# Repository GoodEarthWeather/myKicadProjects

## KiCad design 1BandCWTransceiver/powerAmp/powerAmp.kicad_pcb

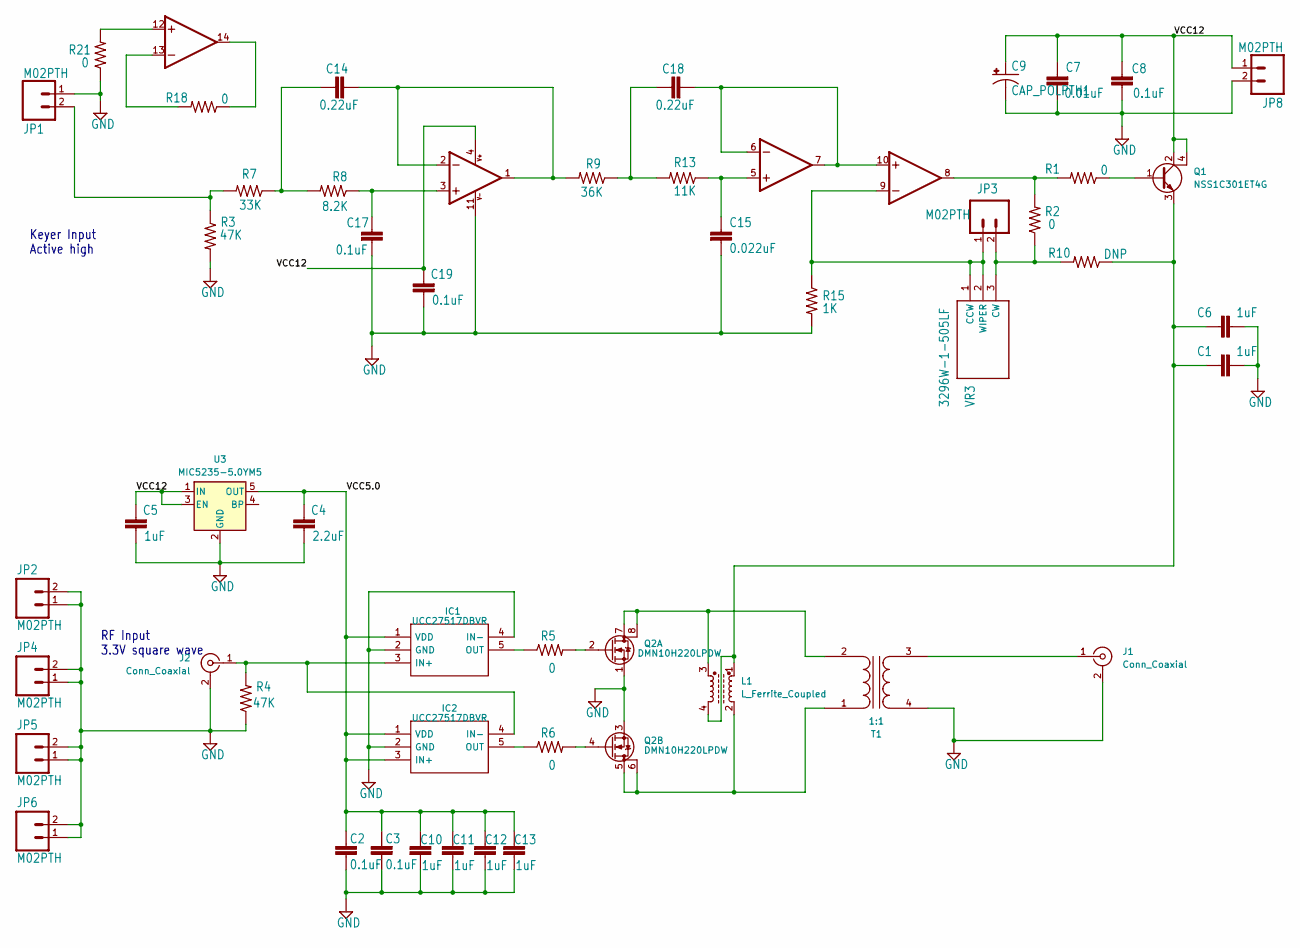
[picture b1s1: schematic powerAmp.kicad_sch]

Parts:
C1, C5, C6, C10, C11, C12, C13: 1uF; C_0603_1608Metric_Pad1.08x0.95mm_HandSolder
C2, C3, C8, C19: 0.1uF; C_0603_1608Metric_Pad1.08x0.95mm_HandSolder
C4: 2.2uF; C_0603_1608Metric_Pad1.08x0.95mm_HandSolder
C7: 0.01uF; C_0603_1608Metric_Pad1.08x0.95mm_HandSolder
C9: CAP_POLPTH1; C_Radial_D5.0mm_H11.0mm_P2.00mm
C14, C18: 710-885012206073; C_0603_1608Metric_Pad1.08x0.95mm_HandSolder
C15: 80-C0603C223K3R; C_0603_1608Metric_Pad1.08x0.95mm_HandSolder
C17: 710-885012206071; C_0603_1608Metric_Pad1.08x0.95mm_HandSolder
IC1, IC2: UCC27517DBVR; SOT95P280X145-5N; Mouser Part Number 595-UCC27517DBVR
J1, J2: Conn_Coaxial; SMA_Amphenol_132289_EdgeMount
JP1, JP2, JP3, JP4, JP5, JP6, JP8: M02PTH; PinHeader_1x02_P2.54mm_Vertical
L1: L_Ferrite_Coupled; Transformer_Balun_Amidon-T50
Q1: NSS1C301ET4G; TO-252-3_TabPin4
Q2: DMN10H220LPDW; DMN10H220LPDW13
R1, R2, R18, R21: 0; R_0603_1608Metric_Pad0.98x0.95mm_HandSolder
R3, R4, R7: 603-RC0603FR-0733KL; R_0603_1608Metric_Pad0.98x0.95mm_HandSolder
R5, R6: 603-RC0603FR-0733KL; R_0805_2012Metric_Pad1.20x1.40mm_HandSolder
R8: 603-RC0603FR-078K2L; R_0603_1608Metric_Pad0.98x0.95mm_HandSolder
R9: 603-RC0603FR-0736KL; R_0603_1608Metric_Pad0.98x0.95mm_HandSolder
R10: DNP; R_0603_1608Metric_Pad0.98x0.95mm_HandSolder
R13: 603-RC0603FR-0711KL; R_0603_1608Metric_Pad0.98x0.95mm_HandSolder
R15: 603-RC0603FR-071KL; R_0603_1608Metric_Pad0.98x0.95mm_HandSolder
T1: 1:1; Transformer_Toroid_Horizontal_D14.0mm_Amidon-T50
U3: MIC5235-5.0YM5; SOT-23-5
U$2: OPA1679IDR; SOIC-14_3.9x8.7mm_P1.27mm
VR3: 3296W-1-505LF; Potentiometer_Bourns_3296W_Vertical

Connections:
/VCC5.0: C2.2, C3.2, C4.2, C10.1, C11.1, C12.1, C13.1, IC1.1 (VDD), IC2.1 (VDD), IC2.3 (IN+), U3.5 (OUT)
/VCC12: C5.2, C7.2, C8.2, C9.1 (+), C19.2, JP8.1, Q1.2 (C), Q1.4 (C), U3.1 (IN), U3.3 (EN), U$2.4 (V+)
GND: C1.1, C2.1, C3.1, C4.1, C5.1, C6.1, C7.1, C8.1, C9.2 (-), C10.2, C11.2, C12.2, C13.2, C15.2, C17.2, C19.1, IC1.2 (GND), IC1.4 (IN-), IC2.2 (GND), J1.2 (Ext), J2.2 (Ext), JP1.1, JP2.1, JP2.2, JP4.1, JP4.2, JP5.1, JP5.2, JP6.1, JP6.2, JP8.2, Q2.1 (S), Q2.3 (S), R3.2, R4.1, R15.2, R21.1, T1.4 (SB), U3.2 (GND), U$2.11 (V-)
unnamed: C14.1, R7.1, R8.2
unnamed: C18.1, R9.1, R13.2
unnamed: IC1.3 (IN+), IC2.4 (IN-), J2.1 (In), R4.2
unnamed: IC1.5 (OUT), R5.1
unnamed: IC2.5 (OUT), R6.1
unnamed: J1.1 (In), T1.3 (SA)
unnamed: JP1.2, R3.1, R7.2
unnamed: Q1.1 (B), R1.1
unnamed: C1.2, C6.2, L1.1, L1.4, Q1.3 (E), R10.1
unnamed: Q2.2 (G), R5.2
unnamed: Q2.4 (G), R6.2
unnamed: L1.2, Q2.5 (D), Q2.6 (D), T1.1 (AA)
unnamed: L1.3, Q2.7 (D), Q2.8 (D), T1.2 (AB)
unnamed: C17.1, R8.1, U$2.3 (+IN)
unnamed: C14.2, R9.2, U$2.1 (OUT), U$2.2 (-IN)
unnamed: C15.1, R13.1, U$2.5 (+IN)
unnamed: C18.2, U$2.6 (-IN), U$2.7 (OUT), U$2.10 (+IN)
unnamed: JP3.1, R15.1, U$2.9 (-IN), VR3.1 (CCW), VR3.2 (WIPER)
unnamed: R1.2, R2.2, U$2.8 (OUT)
unnamed: R21.2, U$2.12 (+IN)
unnamed: R18.2, U$2.13 (-IN)
unnamed: R18.1, U$2.14 (OUT)
unnamed: JP3.2, R2.1, R10.2, VR3.3 (CW)

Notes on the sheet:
RF Input 3.3V square wave
Keyer Input Active high

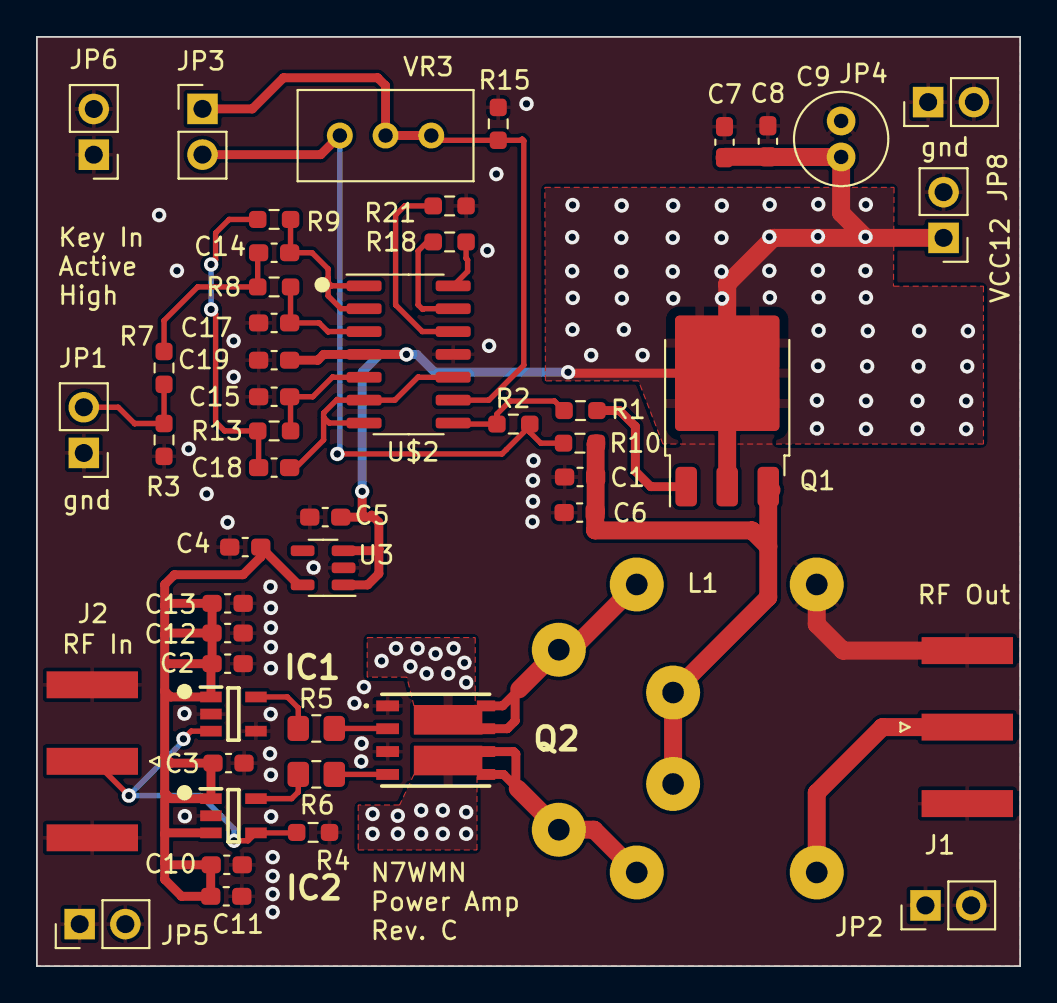
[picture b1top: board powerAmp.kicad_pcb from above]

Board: 2 copper layers, 54.6 x 51.6 mm, 50 parts (1 on the bottom side), 26 nets.

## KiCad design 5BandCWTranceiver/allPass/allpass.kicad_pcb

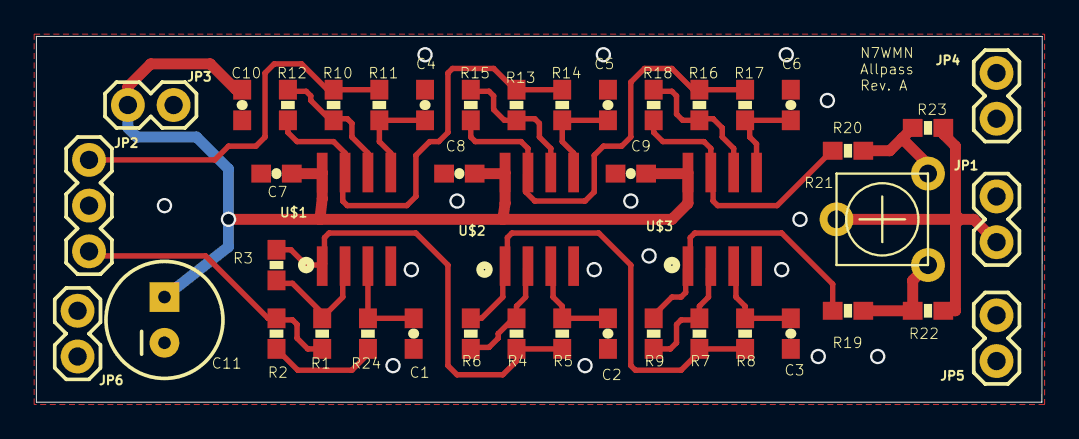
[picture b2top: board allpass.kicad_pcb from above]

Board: 2 copper layers, 55.9 x 20.3 mm, 44 parts (0 on the bottom side), 26 nets.

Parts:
C1, C2, C3, C4, C5, C6: 0.01uF; 0603-CAP
C7, C8, C9, C10: 0.1uF; 0603-CAP
C11: 100uF; CPOL-RADIAL-100UF-25V
JP1, JP3, JP4, JP5, JP6: M02PTH; 1X02
JP2: 1X03
R1, R3, R4, R6, R7, R9, R10, R12, R13, R15, R16, R18: 10K; 0603-RES
R2: 1.5K; 0603-RES
R5: 11.3K; 0603-RES
R8: 51.1K; 0603-RES
R11: 5.23K; 0603-RES
R14: 23.2K; 0603-RES
R17: 178K; 0603-RES
R19, R20: 4.7K; 0603-RES
R21: TRIMPOTPTH; TRIM_POT_PTH
R22, R23: 0; 0603-RES
R24: 200; 0603-RES
U$1, U$2, U$3: LM4562; SOIC8

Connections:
GND: C1.2, C2.2, C3.2, C4.2, C5.2, C6.2, C7.2, C8.2, C9.2, C10.2, C11.2, JP1.2, JP2.2, JP3.2, JP4.1, JP4.2, JP5.1, JP5.2, JP6.1, JP6.2, U$1.4, U$2.4, U$3.4
unnamed: R2.2, R24.1
unnamed: C1.1, R24.2, U$1.3
unnamed: R1.2, R3.1, U$1.2
unnamed: R3.2, R4.1, R5.1, U$1.1
unnamed: R4.2, R6.1, U$2.2
unnamed: C2.1, R5.2, U$2.3
unnamed: R15.2, R16.1, R17.1, U$2.7
unnamed: R6.2, R7.1, R8.1, U$2.1
unnamed: R7.2, R9.1, U$3.2
unnamed: C3.1, R8.2, U$3.3
unnamed: R16.2, R18.1, U$3.6
unnamed: R9.2, R19.1, U$3.1
unnamed: R10.2, R12.1, U$1.6
unnamed: C4.1, R11.2, U$1.5
unnamed: C6.1, R17.2, U$3.5
unnamed: R12.2, R13.1, R14.1, U$1.7
unnamed: R13.2, R15.1, U$2.6
unnamed: C5.1, R14.2, U$2.5
unnamed: R18.2, R20.1, U$3.7
unnamed: JP2.3, R1.1, R2.1
unnamed: JP2.1, R10.1, R11.1
unnamed: R20.2, R21.3, R23.1
unnamed: R19.2, R21.1, R22.2
unnamed: JP1.1, R21.2, R22.1, R23.2
VCC5: C7.1, C8.1, C9.1, C10.1, C11.1, JP3.1, U$1.8, U$2.8, U$3.8

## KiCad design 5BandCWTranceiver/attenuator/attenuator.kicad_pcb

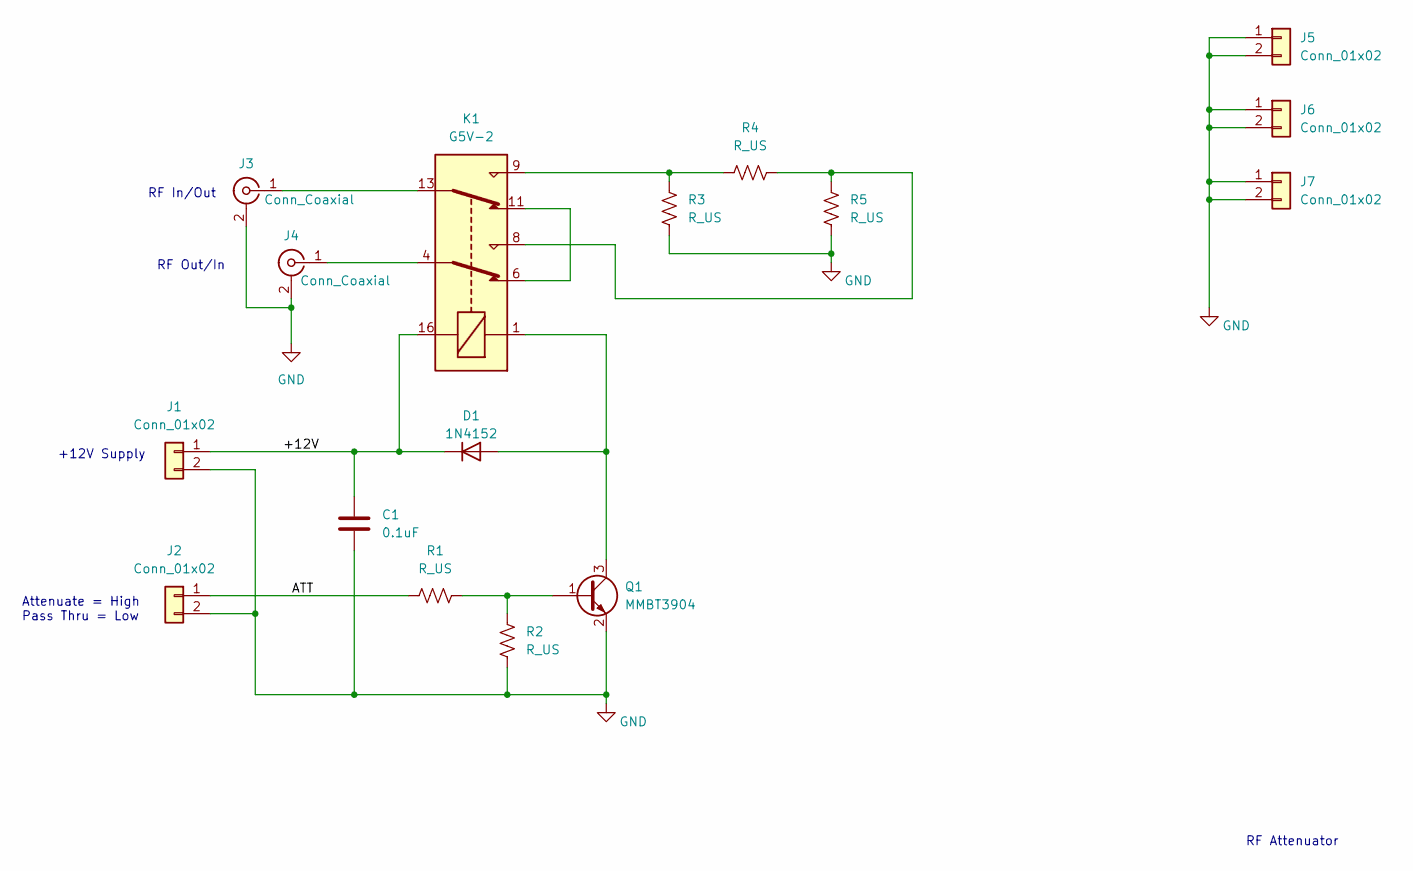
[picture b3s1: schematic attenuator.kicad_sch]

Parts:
C1: 0.1uF; C_0603_1608Metric_Pad1.08x0.95mm_HandSolder
D1: 1N4152; D_DO-41_SOD81_P7.62mm_Horizontal
J1, J2, J5, J6, J7: Conn_01x02; PinHeader_1x02_P2.54mm_Vertical
J3, J4: Conn_Coaxial; SMA_Samtec_SMA-J-P-X-ST-EM1_EdgeMount
K1: G5V-2; Relay_DPDT_Omron_G5V-2
Q1: MMBT3904; SOT-23
R1, R2, R3, R4, R5: R_US; R_0603_1608Metric_Pad0.98x0.95mm_HandSolder

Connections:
/+12V: C1.1, D1.1 (K), J1.1, K1.16
/ATT: J2.1, R1.1
GND: C1.2, J1.2, J2.2, J3.2 (Ext), J4.2 (Ext), J5.1, J5.2, J6.1, J6.2, J7.1, J7.2, Q1.2 (E), R2.2, R3.2, R5.2
unnamed: D1.2 (A), K1.1, Q1.3 (C)
unnamed: J3.1 (In), K1.13
unnamed: J4.1 (In), K1.4
unnamed: K1.8, R4.2, R5.1
unnamed: K1.9, R3.1, R4.1
unnamed: K1.6, K1.11
unnamed: Q1.1 (B), R1.2, R2.1

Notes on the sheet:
RF Out/In
RF Attenuator
Attenuate = High Pass Thru = Low
RF In/Out
+12V Supply

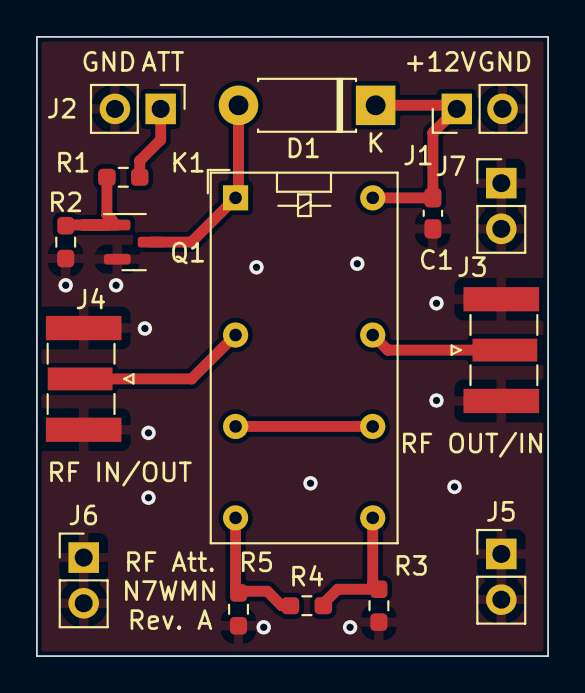
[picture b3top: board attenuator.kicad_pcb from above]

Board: 2 copper layers, 28.4 x 34.4 mm, 16 parts (0 on the bottom side), 10 nets.

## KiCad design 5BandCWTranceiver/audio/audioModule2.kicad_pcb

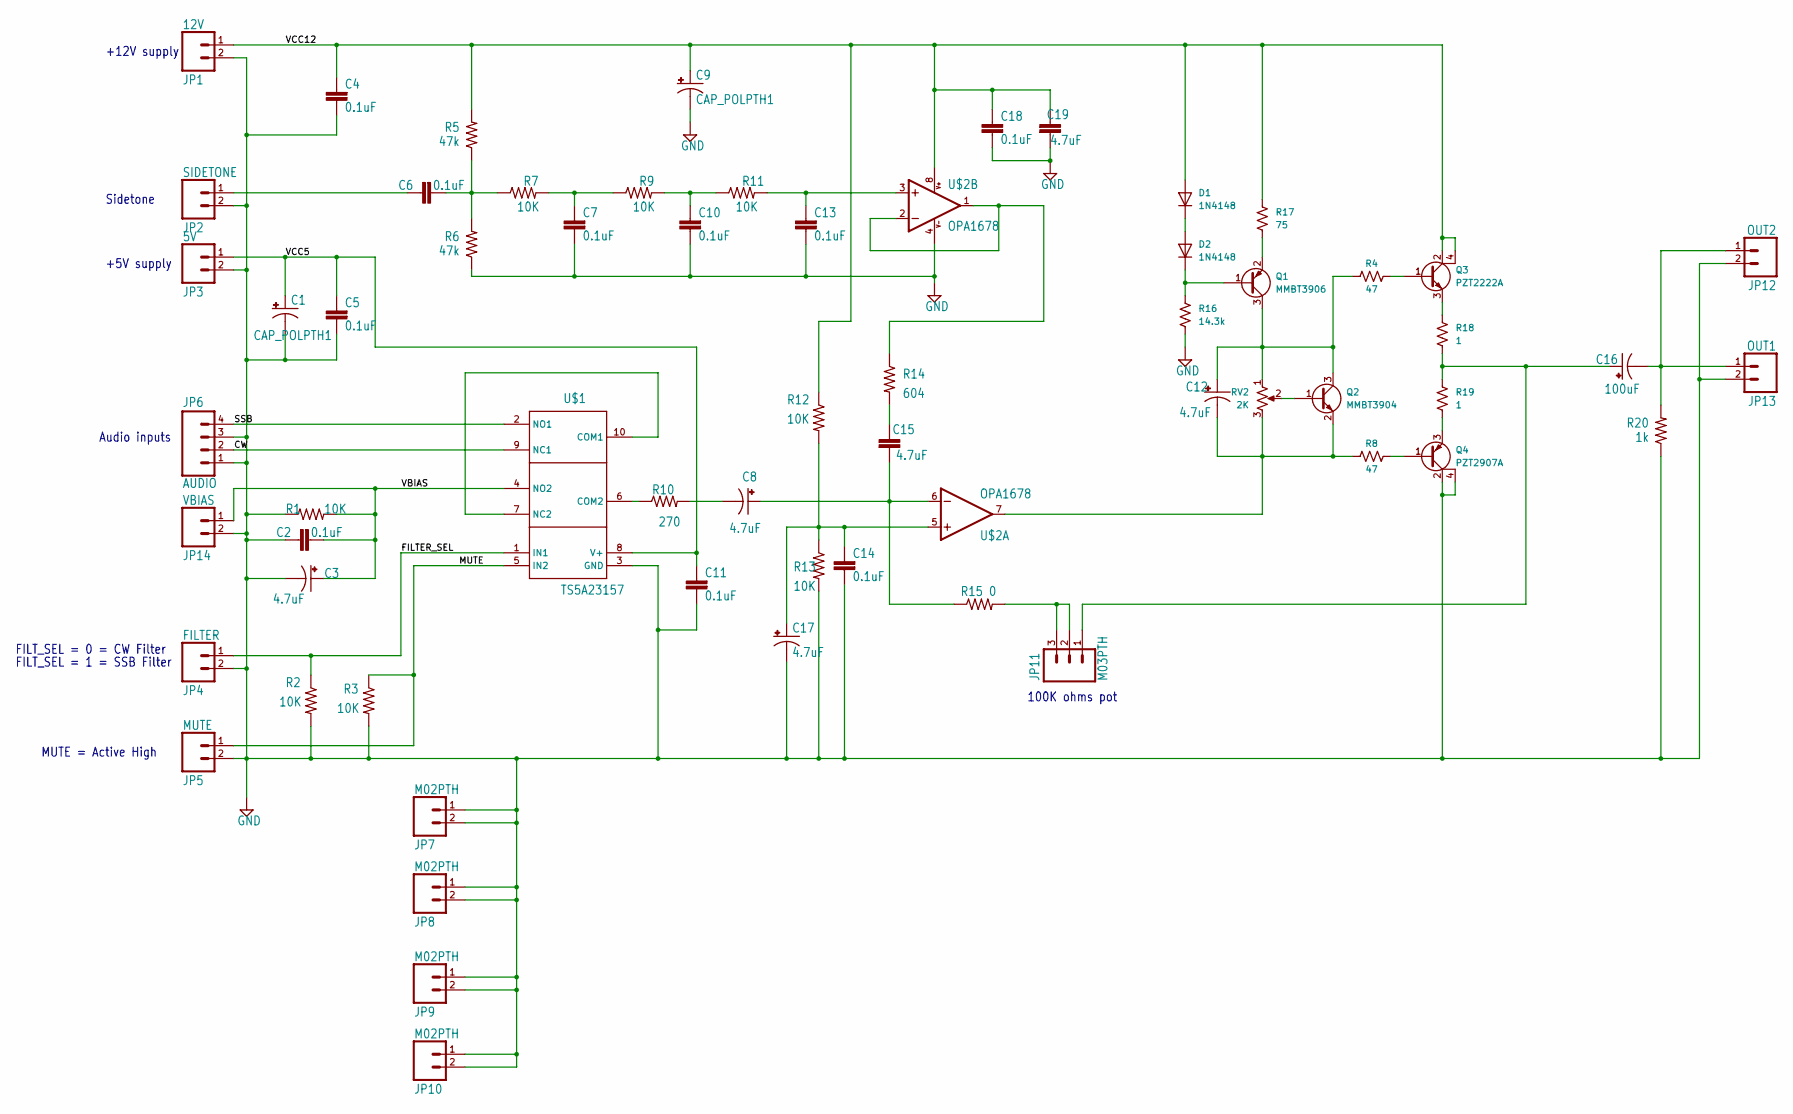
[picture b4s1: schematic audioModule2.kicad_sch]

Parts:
C1, C9: CAP_POLPTH1; CP_Radial_D6.3mm_P2.50mm
C2, C4, C5, C6, C7, C10, C11, C13, C14, C18: 0.1uF; C_0603_1608Metric_Pad1.08x0.95mm_HandSolder
C3, C8, C12, C17: 4.7uF; CP_Radial_D6.3mm_P2.50mm
C15, C19: 4.7uF; C_0603_1608Metric_Pad1.08x0.95mm_HandSolder
C16: 100uF; CP_Radial_D6.3mm_P2.50mm
D1, D2: 1N4148; D_DO-35_SOD27_P7.62mm_Horizontal
JP1: 12V; PinHeader_1x02_P2.54mm_Vertical
JP2: SIDETONE; PinHeader_1x02_P2.54mm_Vertical
JP3: 5V; PinHeader_1x02_P2.54mm_Vertical
JP4: FILTER; PinHeader_1x02_P2.54mm_Vertical
JP5: MUTE; PinHeader_1x02_P2.54mm_Vertical
JP6: AUDIO; PinHeader_1x04_P2.54mm_Vertical
JP7, JP8, JP9, JP10: M02PTH; PinHeader_1x02_P2.54mm_Vertical
JP11: M03PTH; PinHeader_1x03_P2.54mm_Vertical
JP12: OUT2; PinHeader_1x02_P2.54mm_Vertical
JP13: OUT1; PinHeader_1x02_P2.54mm_Vertical
JP14: VBIAS; PinHeader_1x02_P2.54mm_Vertical
Q1: MMBT3906; SOT-23
Q2: MMBT3904; SOT-23
Q3: PZT2222A; SOT-223
Q4: PZT2907A; SOT-223
R1, R2, R3, R7, R9, R11, R12, R13: 10K; R_0603_1608Metric_Pad0.98x0.95mm_HandSolder
R4, R8: 47; R_0805_2012Metric_Pad1.20x1.40mm_HandSolder
R5, R6: 47k; R_0603_1608Metric_Pad0.98x0.95mm_HandSolder
R10: 270; R_0603_1608Metric_Pad0.98x0.95mm_HandSolder
R14: 604; R_0603_1608Metric_Pad0.98x0.95mm_HandSolder
R15: 0; R_0603_1608Metric_Pad0.98x0.95mm_HandSolder
R16: 14.3k; R_0603_1608Metric_Pad0.98x0.95mm_HandSolder
R17: 75; R_0603_1608Metric_Pad0.98x0.95mm_HandSolder
R18, R19: 1; R_0805_2012Metric_Pad1.20x1.40mm_HandSolder
R20: 1k; R_0603_1608Metric_Pad0.98x0.95mm_HandSolder
RV2: 2K; Potentiometer_Bourns_3296W_Vertical
U$1: TS5A23157; MSOP10
U$2: OPA1678; SOIC-8_3.9x4.9mm_P1.27mm

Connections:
/CW: JP6.2, U$1.9 (NC1)
/FILTER_SEL: JP4.1, R2.1, U$1.1 (IN1)
/MUTE: JP5.1, R3.1, U$1.5 (IN2)
/SSB: JP6.4, U$1.2 (NO1)
/VBIAS: C2.1, C3.1 (+), JP14.1, R1.2, U$1.4 (NO2)
/VCC5: C1.1 (+), C5.2, C11.2, JP3.1, U$1.8 (V+)
/VCC12: C4.2, C9.1 (+), C18.2, C19.1, D1.2 (A), JP1.1, Q3.2 (C), Q3.4 (C), R5.2, R12.1, R17.1, U$2.8 (V+)
GND: C1.2 (-), C2.2, C3.2 (-), C4.1, C5.1, C7.1, C9.2 (-), C10.1, C11.1, C13.1, C14.1, C17.2 (-), C18.1, C19.2, JP1.2, JP2.2, JP3.2, JP4.2, JP5.2, JP6.1, JP6.3, JP7.1, JP7.2, JP8.1, JP8.2, JP9.1, JP9.2, JP10.1, JP10.2, JP12.2, JP13.2, JP14.2, Q4.2 (C), Q4.4 (C), R1.1, R2.2, R3.2, R6.1, R13.2, R16.2, R20.1, U$1.3 (GND), U$2.4 (V-)
unnamed: C6.1, R5.1, R6.2, R7.1
unnamed: C6.2, JP2.1
unnamed: C7.2, R7.2, R9.1
unnamed: C10.2, R9.2, R11.1
unnamed: C13.2, R11.2, U$2.3 (+IN)
unnamed: C14.2, C17.1 (+), R12.2, R13.1, U$2.5 (+IN)
unnamed: C15.1, R14.2
unnamed: C8.1 (+), C15.2, R15.1, U$2.6 (-IN)
unnamed: C16.1 (+), JP11.1, R18.2, R19.1
unnamed: C16.2 (-), JP12.1, JP13.1, R20.2
unnamed: D1.1 (K), D2.2 (A)
unnamed: D2.1 (K), Q1.1 (B), R16.1
unnamed: JP11.2, JP11.3, R15.2
unnamed: Q1.2 (E), R17.2
unnamed: C12.1 (+), Q1.3 (C), Q2.3 (C), R4.1, RV2.1
unnamed: Q2.1 (B), RV2.2
unnamed: C12.2 (-), Q2.2 (E), R8.1, RV2.3, U$2.7 (OUT)
unnamed: Q3.1 (B), R4.2
unnamed: Q3.3 (E), R18.1
unnamed: Q4.1 (B), R8.2
unnamed: Q4.3 (E), R19.2
unnamed: R10.1, U$1.6 (COM2)
unnamed: C8.2 (-), R10.2
unnamed: U$1.7 (NC2), U$1.10 (COM1)
unnamed: R14.1, U$2.1 (OUT), U$2.2 (-IN)

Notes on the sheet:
Sidetone
+5V supply
Audio inputs
100K ohms pot
MUTE = Active High
FILT_SEL = 0 = CW Filter
+12V supply
FILT_SEL = 1 = SSB Filter

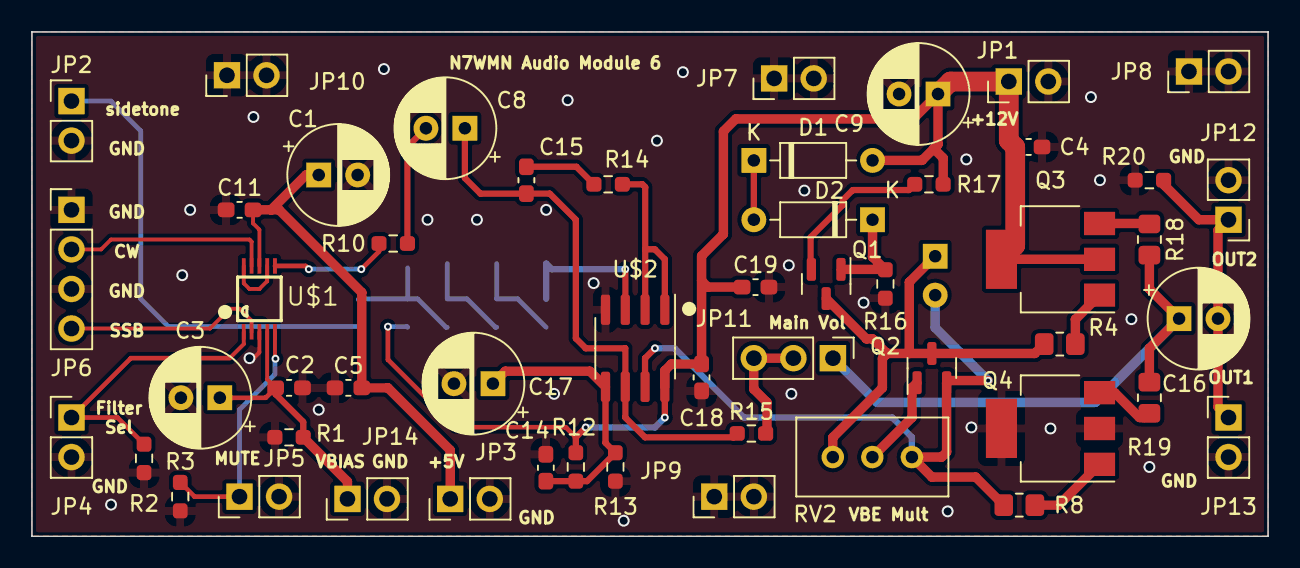
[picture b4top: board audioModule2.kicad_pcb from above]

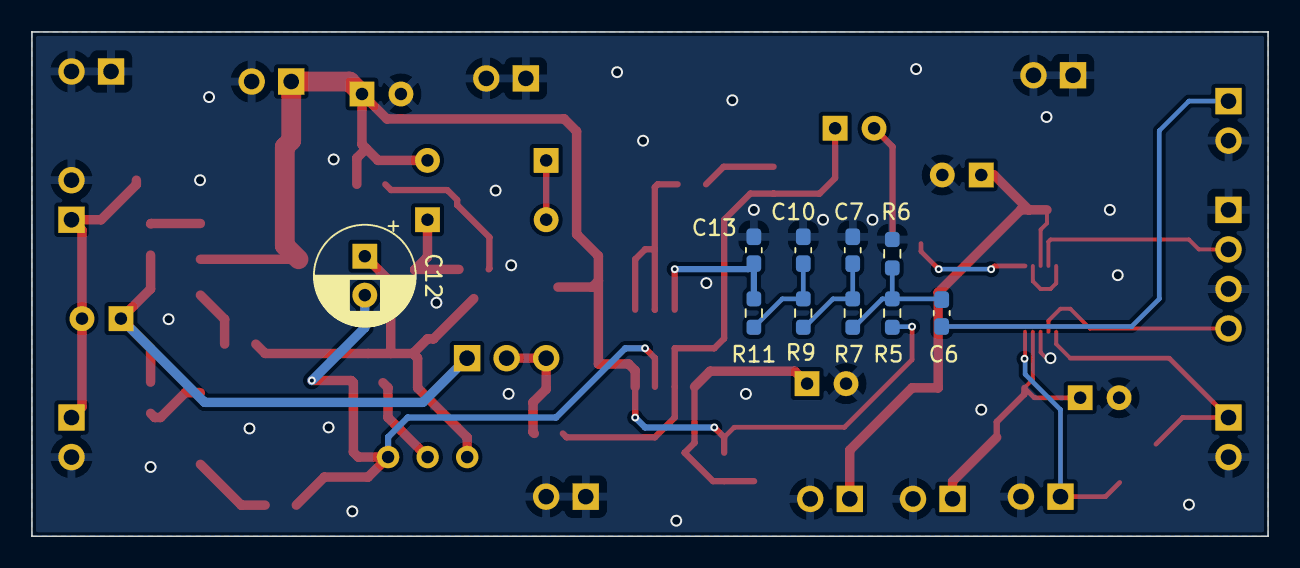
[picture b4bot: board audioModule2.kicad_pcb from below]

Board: 2 copper layers, 79.4 x 32.4 mm, 62 parts (10 on the bottom side), 33 nets.

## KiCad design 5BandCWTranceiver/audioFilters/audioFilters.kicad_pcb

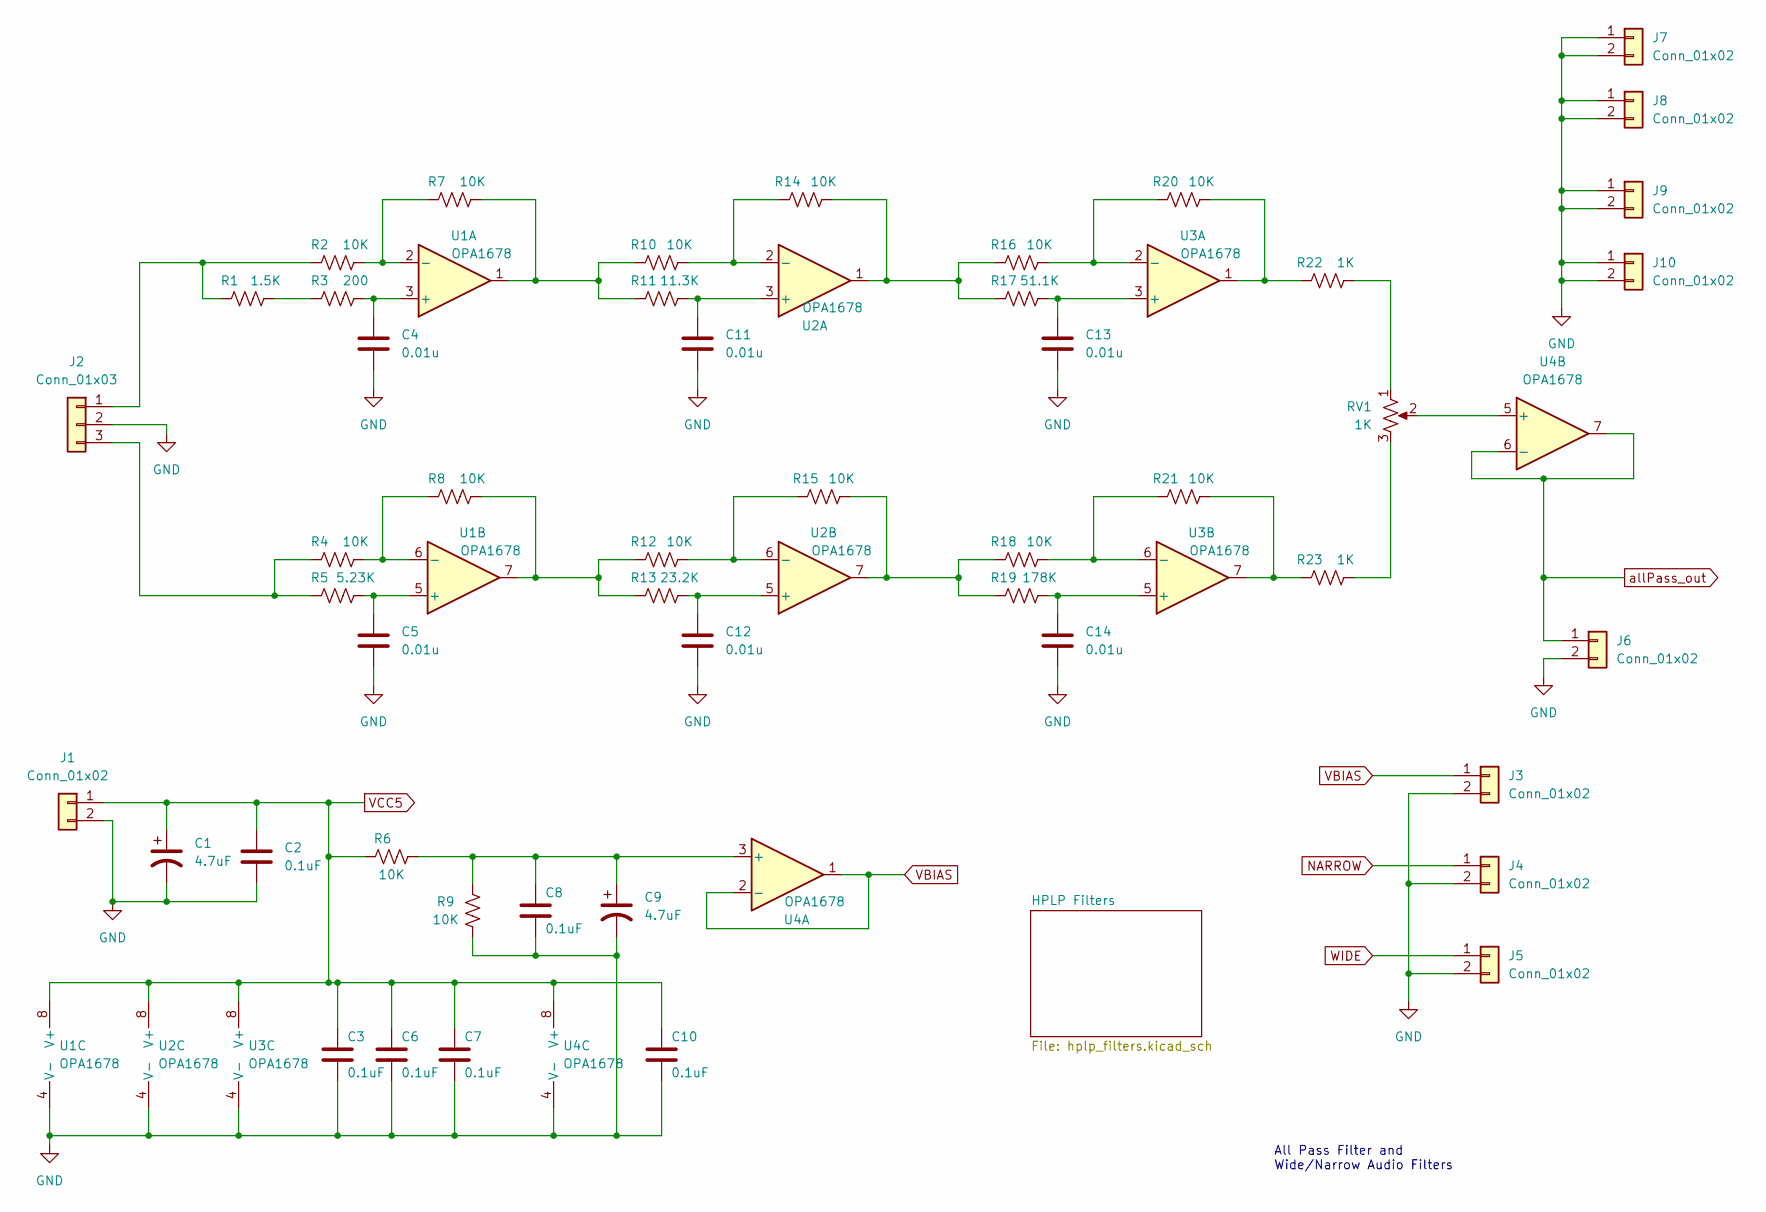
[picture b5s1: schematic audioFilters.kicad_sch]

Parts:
C1, C9: 4.7uF; CP_Radial_D5.0mm_P2.50mm
C2, C3, C6, C7, C8, C10: 0.1uF; C_0603_1608Metric_Pad1.08x0.95mm_HandSolder
C4, C5, C11, C12, C13, C14: 0.01u; C_0603_1608Metric_Pad1.08x0.95mm_HandSolder
J1, J3, J4, J5, J6, J7, J8, J9, J10: Conn_01x02; PinHeader_1x02_P2.54mm_Vertical
J2: Conn_01x03; PinHeader_1x03_P2.54mm_Vertical
R1: 1.5K; R_0603_1608Metric_Pad0.98x0.95mm_HandSolder
R2, R4, R6, R7, R8, R9, R10, R12, R14, R15, R16, R18, R20, R21: 10K; R_0603_1608Metric_Pad0.98x0.95mm_HandSolder
R3: 200; R_0603_1608Metric_Pad0.98x0.95mm_HandSolder
R5: 5.23K; R_0603_1608Metric_Pad0.98x0.95mm_HandSolder
R11: 11.3K; R_0603_1608Metric_Pad0.98x0.95mm_HandSolder
R13: 23.2K; R_0603_1608Metric_Pad0.98x0.95mm_HandSolder
R17: 51.1K; R_0603_1608Metric_Pad0.98x0.95mm_HandSolder
R19: 178K; R_0603_1608Metric_Pad0.98x0.95mm_HandSolder
R22, R23: 1K; R_0603_1608Metric_Pad0.98x0.95mm_HandSolder
RV1: 1K; Potentiometer_Bourns_3296W_Vertical
U1, U2: OPA1678
U3, U4: OPA1678; SOIC-8_3.9x4.9mm_P1.27mm

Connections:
GND: C1.2, C2.2, C3.2, C4.2, C5.2, C6.2, C7.2, C8.2, C9.2, C10.2, C11.2, C12.2, C13.2, C14.2, J1.2, J2.2, J3.2, J4.2, J5.2, J6.2, J7.1, J7.2, J8.1, J8.2, J9.1, J9.2, J10.1, J10.2, R9.1, U1.4 (V-), U2.4 (V-), U3.4 (V-), U4.4 (V-); also elsewhere on the board
NARROW: J4.1; also elsewhere on the board
unnamed: C4.1, R3.2, U1.3 (+)
unnamed: C5.1, R5.2, U1.5 (+)
unnamed: C8.1, C9.1, R6.2, R9.2, U4.3 (+)
unnamed: C11.1, R11.2, U2.3 (+)
unnamed: C12.1, R13.2, U2.5 (+)
unnamed: C13.1, R17.2, U3.3 (+)
unnamed: C14.1, R19.2, U3.5 (+)
unnamed: J2.1, R1.1, R2.1
unnamed: J2.3, R4.1, R5.1
unnamed: R1.2, R3.1
unnamed: R2.2, R7.1, U1.2 (-)
unnamed: R4.2, R8.1, U1.6 (-)
unnamed: R7.2, R10.1, R11.1, U1.1
unnamed: R10.2, R14.1, U2.2 (-)
unnamed: R8.2, R12.1, R13.1, U1.7
unnamed: R12.2, R15.1, U2.6 (-)
unnamed: R14.2, R16.1, R17.1, U2.1
unnamed: R15.2, R18.1, R19.1, U2.7
unnamed: R16.2, R20.1, U3.2 (-)
unnamed: R18.2, R21.1, U3.6 (-)
unnamed: R20.2, R22.1, U3.1
unnamed: R21.2, R23.1, U3.7
unnamed: R22.2, RV1.1
unnamed: R23.2, RV1.3
unnamed: RV1.2, U4.5 (+)
VBIAS: J3.1, U4.1, U4.2 (-); also elsewhere on the board
VCC5: C1.1, C2.1, C3.1, C6.1, C7.1, C10.1, J1.1, R6.1, U1.8 (V+), U2.8 (V+), U3.8 (V+), U4.8 (V+); also elsewhere on the board
WIDE: J5.1; also elsewhere on the board
allPass_out: J6.1, U4.6 (-), U4.7; also elsewhere on the board

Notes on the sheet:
All Pass Filter and Wide/Narrow Audio Filters

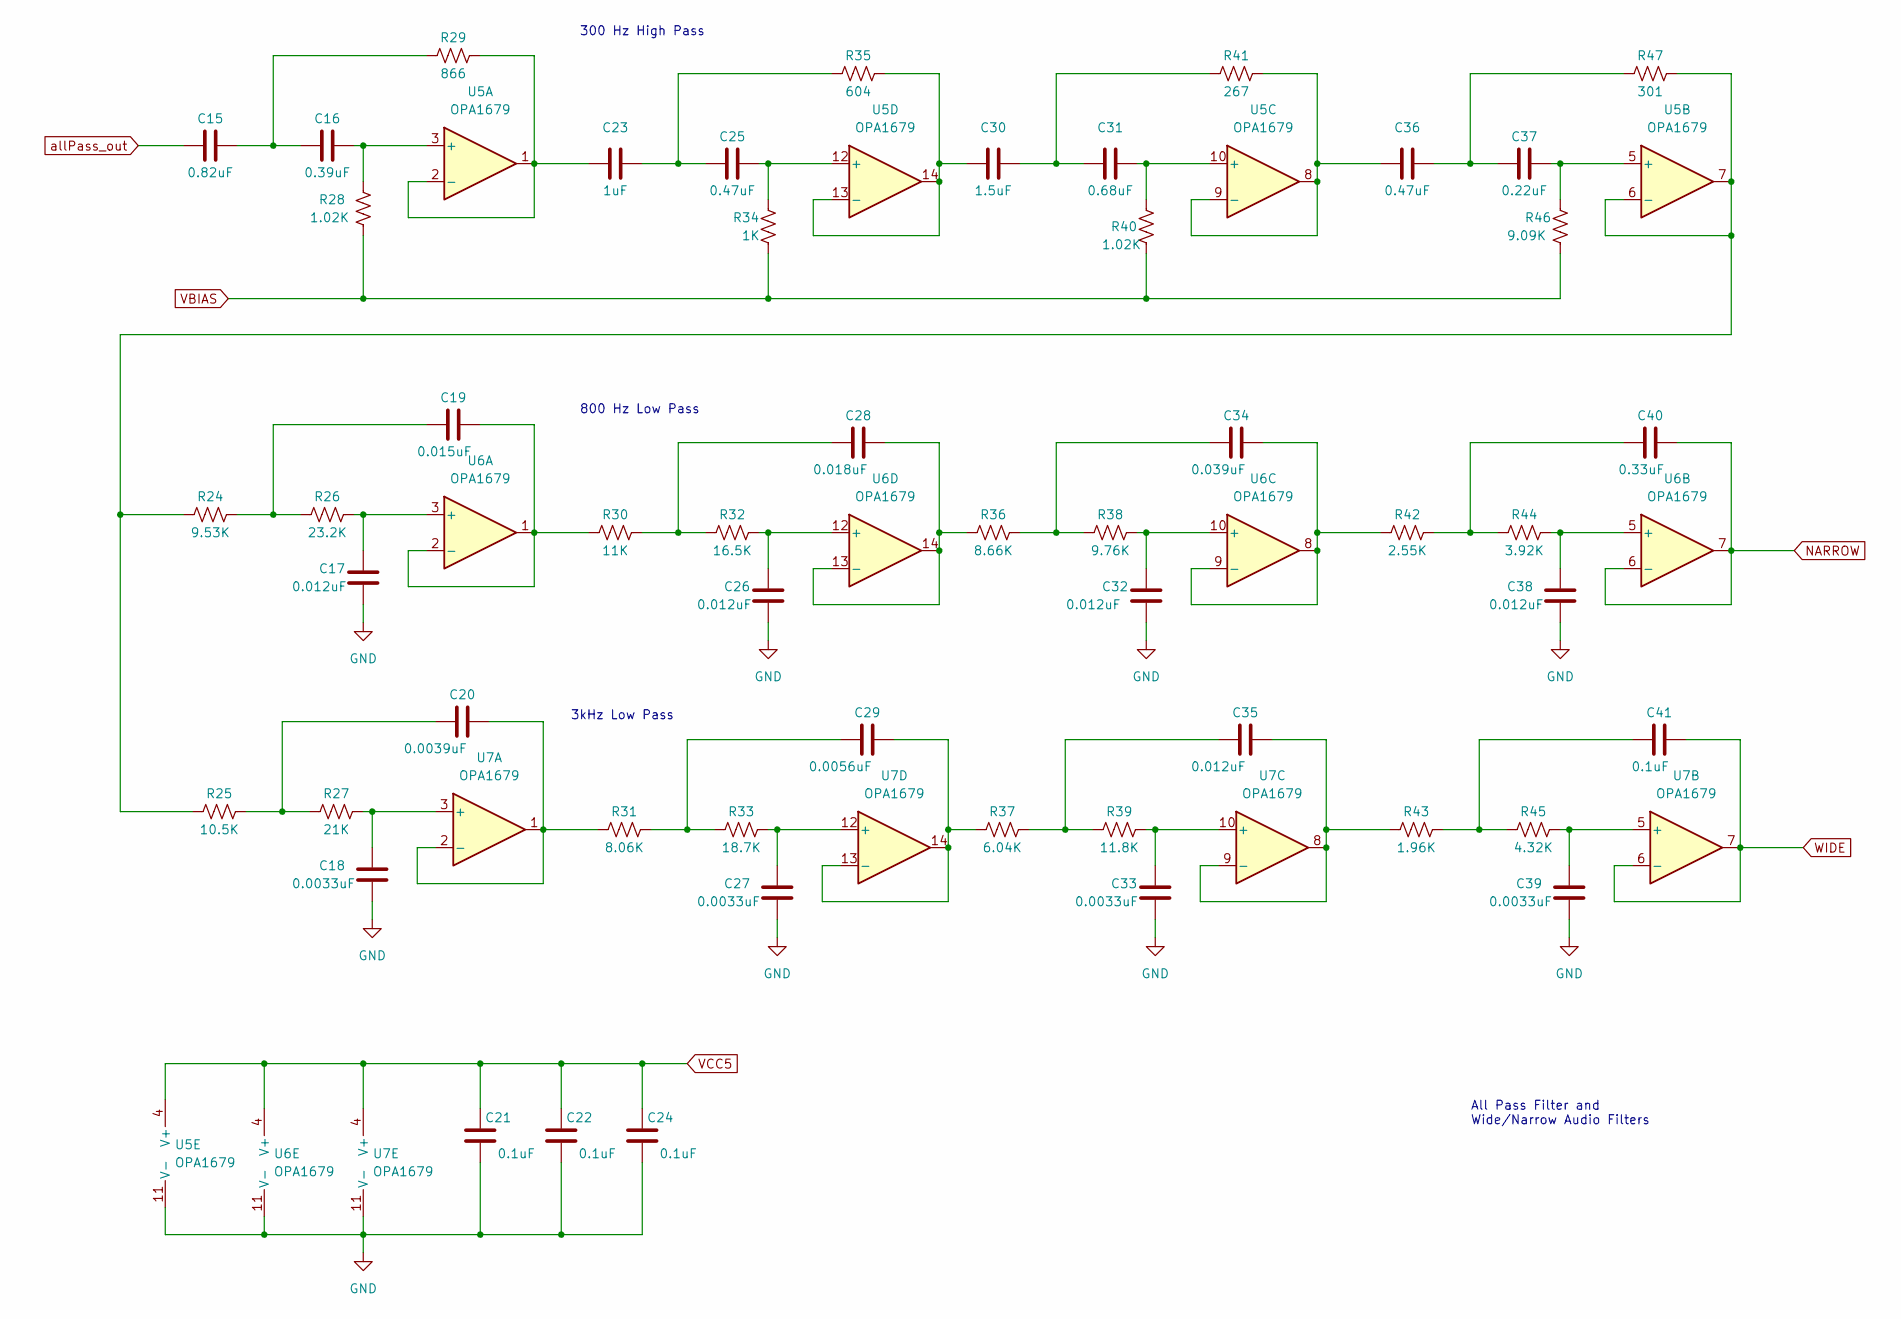
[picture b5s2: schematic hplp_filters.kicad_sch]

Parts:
C15: 0.82uF; C_0603_1608Metric_Pad1.08x0.95mm_HandSolder
C16: 0.39uF; C_0603_1608Metric_Pad1.08x0.95mm_HandSolder
C17, C26, C32, C35, C38: 0.012uF; C_0603_1608Metric_Pad1.08x0.95mm_HandSolder
C18, C27, C33, C39: 0.0033uF; C_0603_1608Metric_Pad1.08x0.95mm_HandSolder
C19: 0.015uF; C_0603_1608Metric_Pad1.08x0.95mm_HandSolder
C20: 0.0039uF; C_0603_1608Metric_Pad1.08x0.95mm_HandSolder
C21, C22, C24, C41: 0.1uF; C_0603_1608Metric_Pad1.08x0.95mm_HandSolder
C23: 1uF; C_0603_1608Metric_Pad1.08x0.95mm_HandSolder
C25, C36: 0.47uF; C_0603_1608Metric_Pad1.08x0.95mm_HandSolder
C28: 0.018uF; C_0603_1608Metric_Pad1.08x0.95mm_HandSolder
C29: 0.0056uF; C_0603_1608Metric_Pad1.08x0.95mm_HandSolder
C30: 1.5uF; C_0603_1608Metric_Pad1.08x0.95mm_HandSolder
C31: 0.68uF; C_0603_1608Metric_Pad1.08x0.95mm_HandSolder
C34: 0.039uF; C_0603_1608Metric_Pad1.08x0.95mm_HandSolder
C37: 0.22uF; C_0603_1608Metric_Pad1.08x0.95mm_HandSolder
C40: 0.33uF; C_0603_1608Metric_Pad1.08x0.95mm_HandSolder
R24: 9.53K; R_0603_1608Metric_Pad0.98x0.95mm_HandSolder
R25: 10.5K; R_0603_1608Metric_Pad0.98x0.95mm_HandSolder
R26: 23.2K; R_0603_1608Metric_Pad0.98x0.95mm_HandSolder
R27: 21K; R_0603_1608Metric_Pad0.98x0.95mm_HandSolder
R28, R40: 1.02K; R_0603_1608Metric_Pad0.98x0.95mm_HandSolder
R29: 866; R_0603_1608Metric_Pad0.98x0.95mm_HandSolder
R30: 11K; R_0603_1608Metric_Pad0.98x0.95mm_HandSolder
R31: 8.06K; R_0603_1608Metric_Pad0.98x0.95mm_HandSolder
R32: 16.5K; R_0603_1608Metric_Pad0.98x0.95mm_HandSolder
R33: 18.7K; R_0603_1608Metric_Pad0.98x0.95mm_HandSolder
R34: 1K; R_0603_1608Metric_Pad0.98x0.95mm_HandSolder
R35: 604; R_0603_1608Metric_Pad0.98x0.95mm_HandSolder
R36: 8.66K; R_0603_1608Metric_Pad0.98x0.95mm_HandSolder
R37: 6.04K; R_0603_1608Metric_Pad0.98x0.95mm_HandSolder
R38: 9.76K; R_0603_1608Metric_Pad0.98x0.95mm_HandSolder
R39: 11.8K; R_0603_1608Metric_Pad0.98x0.95mm_HandSolder
R41: 267; R_0603_1608Metric_Pad0.98x0.95mm_HandSolder
R42: 2.55K; R_0603_1608Metric_Pad0.98x0.95mm_HandSolder
R43: 1.96K; R_0603_1608Metric_Pad0.98x0.95mm_HandSolder
R44: 3.92K; R_0603_1608Metric_Pad0.98x0.95mm_HandSolder
R45: 4.32K; R_0603_1608Metric_Pad0.98x0.95mm_HandSolder
R46: 9.09K; R_0603_1608Metric_Pad0.98x0.95mm_HandSolder
R47: 301; R_0603_1608Metric_Pad0.98x0.95mm_HandSolder
U5, U7: OPA1679; SOIC-14_3.9x8.7mm_P1.27mm
U6: OPA1679

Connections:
GND: C17.2, C18.2, C21.1, C22.1, C24.1, C26.2, C27.2, C32.2, C33.2, C38.2, C39.2, U5.11 (V-), U6.11 (V-), U7.11 (V-); also elsewhere on the board
NARROW: C40.2, U6.6 (-), U6.7; also elsewhere on the board
unnamed: C15.2, C16.1, R29.1
unnamed: C16.2, R28.2, U5.3 (+)
unnamed: C17.1, R26.2, U6.3 (+)
unnamed: C18.1, R27.2, U7.3 (+)
unnamed: C19.1, R24.2, R26.1
unnamed: C19.2, R30.1, U6.1, U6.2 (-)
unnamed: C20.1, R25.2, R27.1
unnamed: C20.2, R31.1, U7.1, U7.2 (-)
unnamed: C23.1, R29.2, U5.1, U5.2 (-)
unnamed: C23.2, C25.1, R35.1
unnamed: C25.2, R34.2, U5.12 (+)
unnamed: C26.1, R32.2, U6.12 (+)
unnamed: C27.1, R33.2, U7.12 (+)
unnamed: C28.1, R30.2, R32.1
unnamed: C28.2, R36.1, U6.13 (-), U6.14
unnamed: C29.1, R31.2, R33.1
unnamed: C29.2, R37.1, U7.13 (-), U7.14
unnamed: C30.1, R35.2, U5.13 (-), U5.14
unnamed: C30.2, C31.1, R41.1
unnamed: C31.2, R40.2, U5.10 (+)
unnamed: C32.1, R38.2, U6.10 (+)
unnamed: C33.1, R39.2, U7.10 (+)
unnamed: C34.1, R36.2, R38.1
unnamed: C34.2, R42.1, U6.8, U6.9 (-)
unnamed: C35.1, R37.2, R39.1
unnamed: C35.2, R43.1, U7.8, U7.9 (-)
unnamed: C36.1, R41.2, U5.8, U5.9 (-)
unnamed: C36.2, C37.1, R47.1
unnamed: C37.2, R46.2, U5.5 (+)
unnamed: C38.1, R44.2, U6.5 (+)
unnamed: C39.1, R45.2, U7.5 (+)
unnamed: C40.1, R42.2, R44.1
unnamed: C41.1, R43.2, R45.1
unnamed: R24.1, R25.1, R47.2, U5.6 (-), U5.7
VBIAS: R28.1, R34.1, R40.1, R46.1; also elsewhere on the board
VCC5: C21.2, C22.2, C24.2, U5.4 (V+), U6.4 (V+), U7.4 (V+); also elsewhere on the board
WIDE: C41.2, U7.6 (-), U7.7; also elsewhere on the board
allPass_out: C15.1; also elsewhere on the board

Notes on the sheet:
All Pass Filter and Wide/Narrow Audio Filters
3kHz Low Pass
300 Hz High Pass
800 Hz Low Pass
